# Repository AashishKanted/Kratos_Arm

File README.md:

# Kratos_Arm
2023-24 Code base for the robotic arm of the Kratos rover

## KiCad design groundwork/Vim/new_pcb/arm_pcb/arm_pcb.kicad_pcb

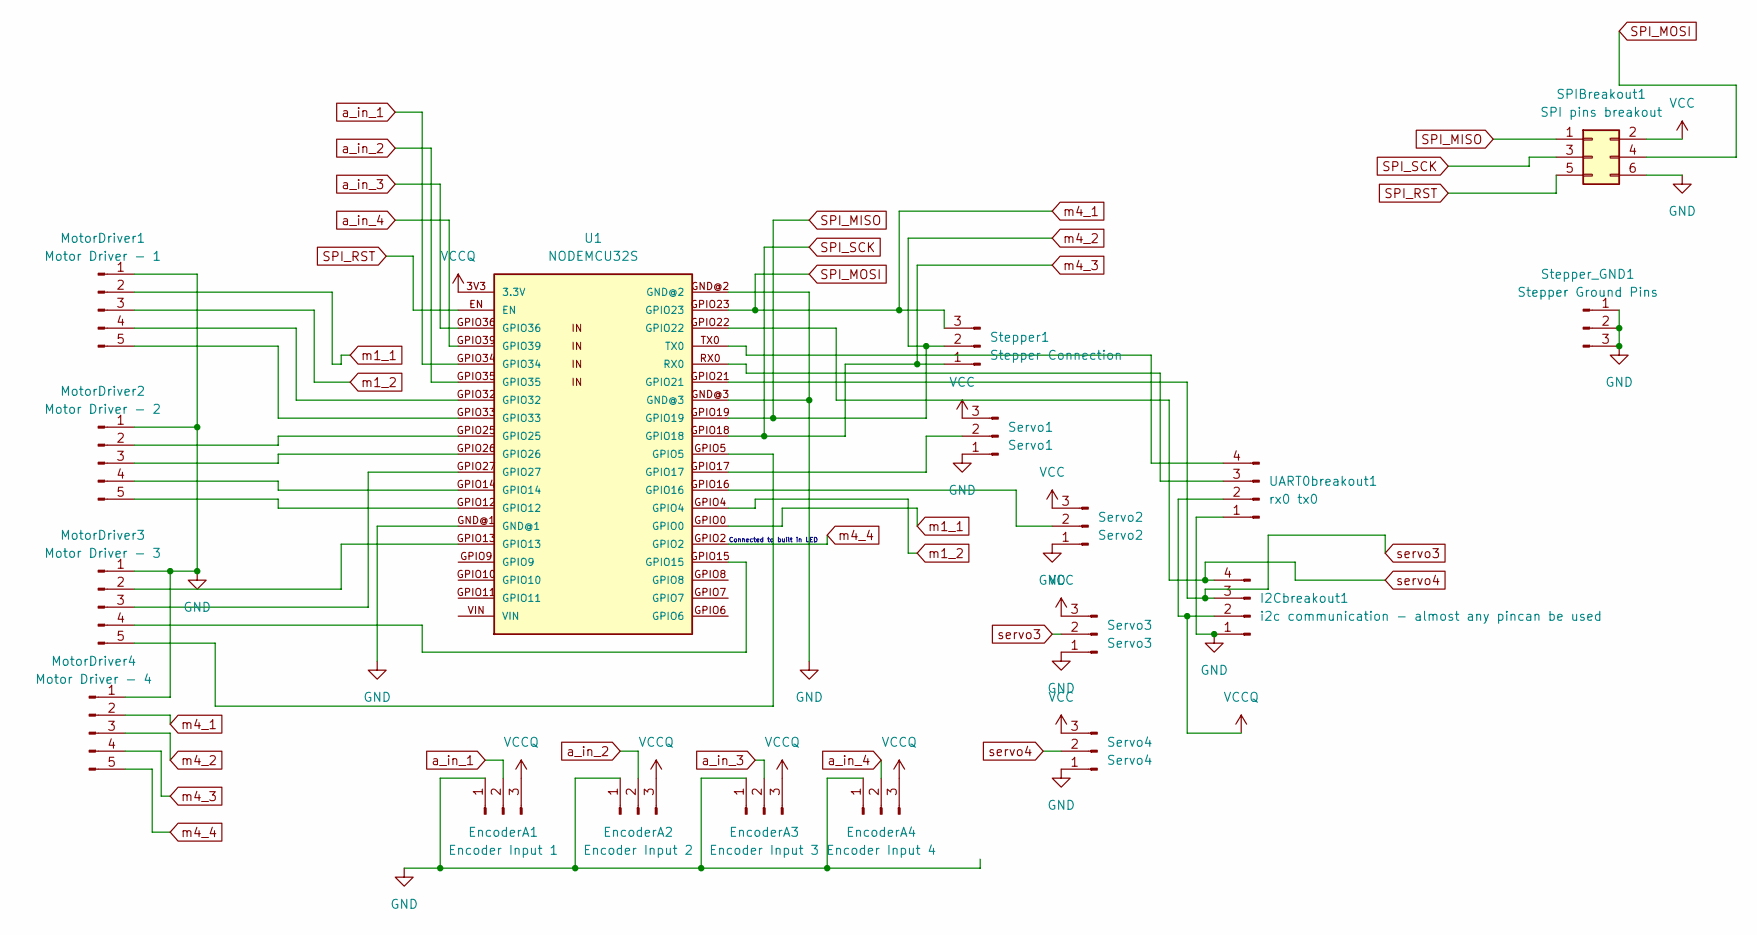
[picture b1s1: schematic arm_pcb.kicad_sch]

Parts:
EncoderA1: Encoder Input 1; JST_XA_B03B-XASK-1-A_1x03_P2.50mm_Vertical
EncoderA2: Encoder Input 2; JST_XA_B03B-XASK-1-A_1x03_P2.50mm_Vertical
EncoderA3: Encoder Input 3; JST_XA_B03B-XASK-1-A_1x03_P2.50mm_Vertical
EncoderA4: Encoder Input 4; JST_XA_B03B-XASK-1-A_1x03_P2.50mm_Vertical
I2Cbreakout1: i2c communication - almost any pincan be used; JST_XA_B04B-XASK-1-A_1x04_P2.50mm_Vertical
MotorDriver1: Motor Driver - 1; JST_XA_B05B-XASK-1-A_1x05_P2.50mm_Vertical
MotorDriver2: Motor Driver - 2; JST_XA_B05B-XASK-1-A_1x05_P2.50mm_Vertical
MotorDriver3: Motor Driver - 3; JST_XA_B05B-XASK-1-A_1x05_P2.50mm_Vertical
MotorDriver4: Motor Driver - 4; JST_XA_B05B-XASK-1-A_1x05_P2.50mm_Vertical
SPIBreakout1: SPI pins breakout; PinHeader_2x03_P2.54mm_Vertical
Servo1: Servo1; JST_XA_B03B-XASK-1-A_1x03_P2.50mm_Vertical
Servo2: Servo2; JST_XA_B03B-XASK-1-A_1x03_P2.50mm_Vertical
Servo3: Servo3; JST_XA_B03B-XASK-1-A_1x03_P2.50mm_Vertical
Servo4: Servo4; JST_XA_B03B-XASK-1-A_1x03_P2.50mm_Vertical
Stepper1: Stepper Connection; JST_XA_B03B-XASK-1-A_1x03_P2.50mm_Vertical
Stepper_GND1: Stepper Ground Pins; JST_XA_B03B-XASK-1-A_1x03_P2.50mm_Vertical
U1: NODEMCU32S
UART0breakout1: rx0 tx0; JST_XA_B04B-XASK-1-A_1x04_P2.50mm_Vertical

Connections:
GND: EncoderA1.1, EncoderA2.1, EncoderA3.1, EncoderA4.1, I2Cbreakout1.1, MotorDriver1.1, MotorDriver2.1, MotorDriver3.1, MotorDriver4.1, SPIBreakout1.6, Servo1.1, Servo2.1, Servo3.1, Servo4.1, Stepper_GND1.1, Stepper_GND1.2, Stepper_GND1.3, U1.GND@1, U1.GND@2, U1.GND@3, UART0breakout1.1; also elsewhere on the board
unnamed: MotorDriver1.4, U1.GPIO32
unnamed: MotorDriver1.5, U1.GPIO33
unnamed: MotorDriver2.2, U1.GPIO25
unnamed: MotorDriver2.3, U1.GPIO26
unnamed: MotorDriver2.4, U1.GPIO14
unnamed: MotorDriver2.5, U1.GPIO12
unnamed: MotorDriver3.2, U1.GPIO13
unnamed: MotorDriver3.3, U1.GPIO27
unnamed: MotorDriver3.4, U1.GPIO15
unnamed: MotorDriver3.5, U1.GPIO5
unnamed: Servo1.2, U1.GPIO17
unnamed: Servo2.2, U1.GPIO16
unnamed: U1.RX0, UART0breakout1.3
unnamed: U1.TX0, UART0breakout1.4
SPI_MISO: MotorDriver4.3, SPIBreakout1.1, Stepper1.2, U1.GPIO19
SPI_MOSI: MotorDriver4.2, SPIBreakout1.4, Stepper1.3, U1.GPIO23
SPI_RST: SPIBreakout1.5, U1.EN
SPI_SCK: MotorDriver4.4, SPIBreakout1.3, Stepper1.1, U1.GPIO18
VCC: SPIBreakout1.2, Servo1.3, Servo2.3, Servo3.3, Servo4.3; also elsewhere on the board
VCCQ: EncoderA1.3, EncoderA2.3, EncoderA3.3, EncoderA4.3, I2Cbreakout1.2, U1.3V3 (3.3V), UART0breakout1.2; also elsewhere on the board
a_in_1: EncoderA1.2, U1.GPIO34
a_in_2: EncoderA2.2, U1.GPIO35
a_in_3: EncoderA3.2, U1.GPIO36
a_in_4: EncoderA4.2, U1.GPIO39
m1_1: MotorDriver1.2, U1.GPIO0
m1_2: MotorDriver1.3, U1.GPIO4
m4_4: MotorDriver4.5, U1.GPIO2
servo3: I2Cbreakout1.3, Servo3.2, U1.GPIO21
servo4: I2Cbreakout1.4, Servo4.2, U1.GPIO22

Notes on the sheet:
Connected to built in LED

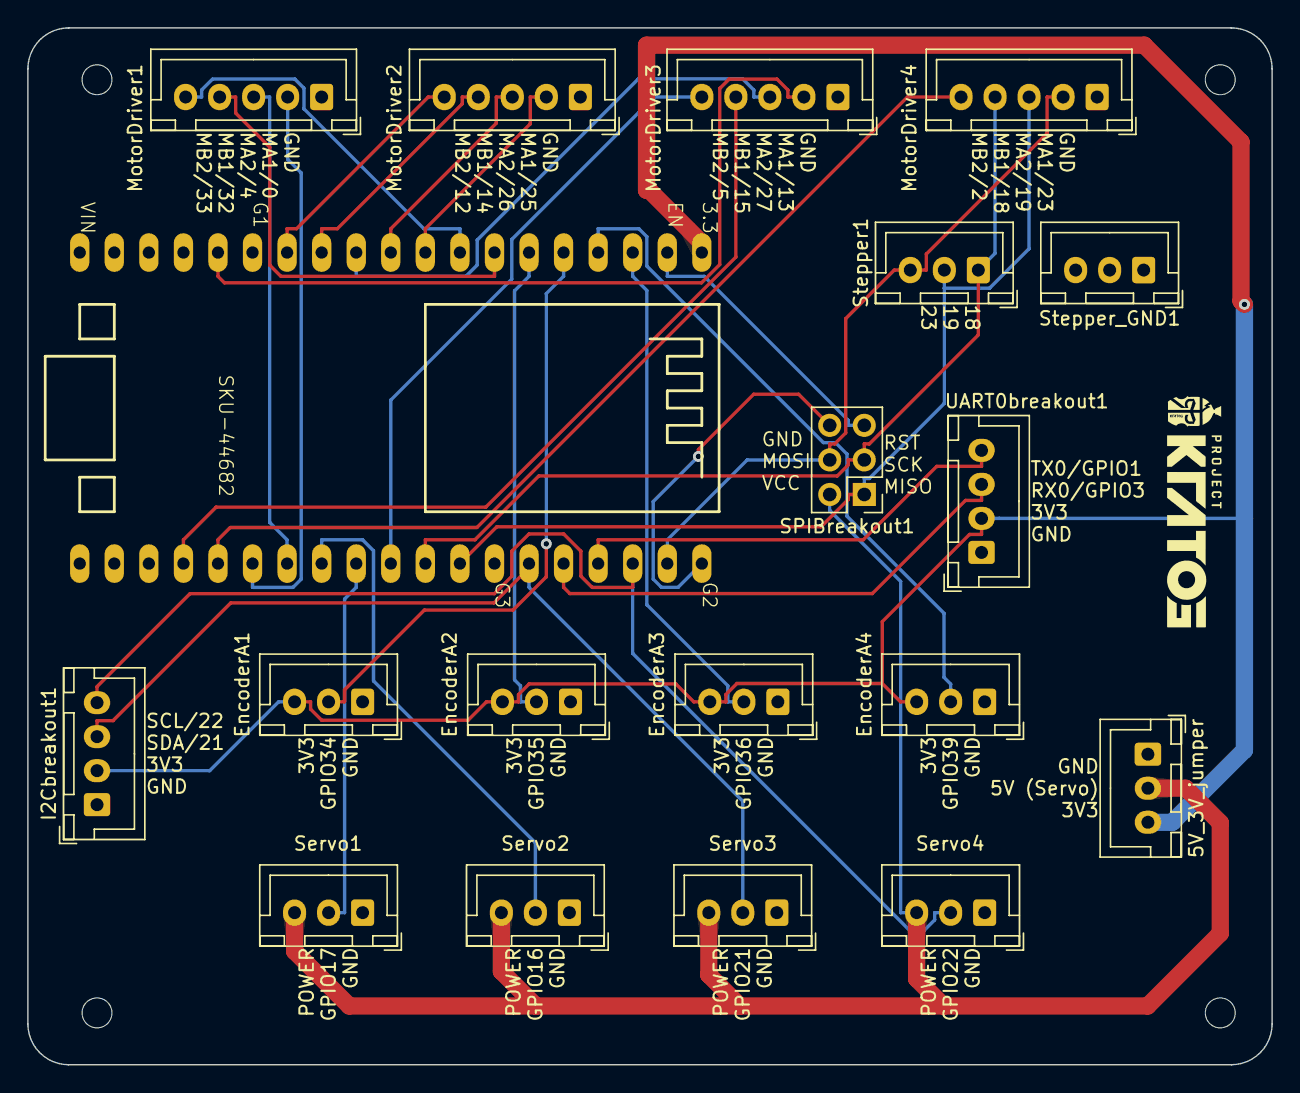
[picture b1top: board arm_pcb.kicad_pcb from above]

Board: 2 copper layers, 91.4 x 76.2 mm, 24 parts (0 on the bottom side), 30 nets.

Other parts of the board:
5V_3V_jumper: JST_XH_B3B-XH-A_1x03_P2.50mm_Vertical
KratosLogo: LOGO
mountinghole1, mountinghole2, mountinghole3, mountinghole4: MountingHole_2.2mm_M2

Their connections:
GND: 5V_3V_jumper.1; also elsewhere on the board
VCC: 5V_3V_jumper.2; also elsewhere on the board
VCCQ: 5V_3V_jumper.3; also elsewhere on the board

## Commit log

2022-11-08 Varad's PUsh
2022-11-08 Push
2022-12-01 Create motor_pid.ino
    Fully functional rhino motor PID
    encoder included
    input - pulse count
2022-12-01 Create inv_k.py
    inverse kinematics
    input - joystick
    output - publishes - pulse count
    prints - degrees
2023-02-15 4 graphs 1 button
2023-02-15 Webcam feed with cancel button
2023-02-16 Publish to different topics using buttons
2023-02-17 Get input through a text box
2023-09-15 Rename readme.me to readme.md
2023-09-16 Add files via upload
    Worksession-1
    Forward/Backward/Stop Motor
2023-09-17 all old code thing
2023-09-19 Rename arm_get_started.ino to arm_get_started.ino
2023-09-19 relocating files
2023-09-21 Add files via upload
    code for arm
2023-09-21 Create readme.md
    created my folder
2023-09-21 change directory structure
2023-09-26 fix directory structure + make a package
2023-09-26 Add files via upload
    speed sensitivity and stepper
2023-09-26 encoder works now
2023-09-27 Create Arduino Codes
2023-10-20 Create inverse kinematics
2023-10-21 Add files via upload
    forward kinematics code
2023-10-24 Add files via upload
    Arduino code for forward kinematics
2023-10-24 Add files via upload
    Changes in documentation
2023-11-01 Renaming files
2023-11-02 for openday
2023-11-03 Create Manan
2023-11-03 final code for gpt type talk for openday
2023-11-05 Create cam_la_v2
2023-11-05 twtrejyt
2023-12-29 First git push for gui
    Sensors window almost complete
2023-12-29 Custom message type for sensor readings
2024-01-07 ML view done
    The pubish button doesn't trigger the script yet (ml values received from a different python script)
2024-01-17 new dev vim
2024-01-18 new dev _ ld almost final _ might change sensor later
2024-01-19 Rename LD_gui.py to kratos_gui.py
2024-01-19 Rename LD_test.py to gui_test.py
2024-01-19 latest gui with bridging py script
    spectral plots half done
2024-01-19 backup in case things go wrong
2024-01-19 spectro fully done
2024-01-22 kinda works
2024-01-22 ld motor setup
2024-01-22 ld motor setup + stepper
2024-01-23 backup incase things go wrong
2024-01-23 new upload
2024-01-23 requirements file
2024-02-13 new pcb designs
2024-02-20 pcb udpate
2024-02-20 pcb schematic udpate final v0.1
2024-02-21 final pcb v0.2
2024-02-21 pcb almost done v0
2024-02-22 pcb done-ishhh
2024-03-26 Feedback from 1 encoder
    Feedback from 1 encoder
2024-04-02 encoder calib script
    works with one orange encoder
    needs conversion factor
2024-04-07 Create ESP codes
